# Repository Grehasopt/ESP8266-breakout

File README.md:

# ESP8266-breakout
A breadboard friendly ESP12E/F breakout with all I/O pins available, flash/reset buttons onboard, and pins ready to use with FTDI module

## License
This project is licensed under the CERN-OHL-S-2.0 (applies from the very first commit on Mar 7, 2021) with the added condition that it may not be used for commercial purposes without prior permission from the license holder.

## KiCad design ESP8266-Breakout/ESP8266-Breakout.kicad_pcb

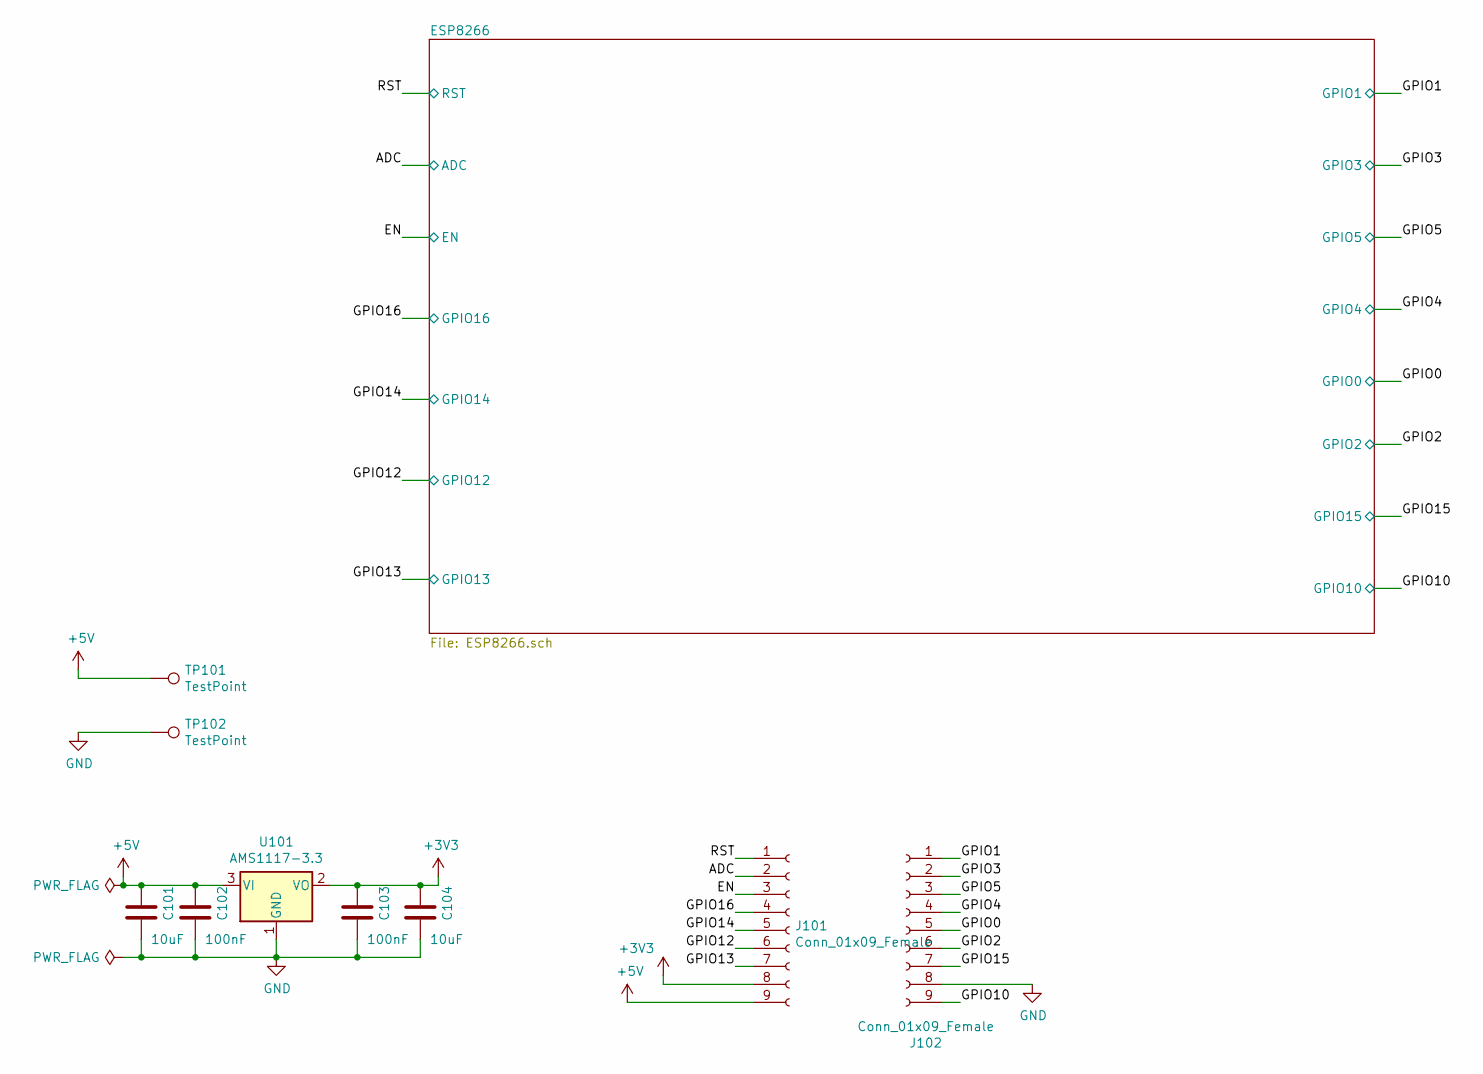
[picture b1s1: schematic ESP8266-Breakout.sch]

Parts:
C101, C104: 10uF; C_1206_3216Metric_Pad1.33x1.80mm_HandSolder; LCSC C13585
C102, C103: 100nF; C_1206_3216Metric_Pad1.33x1.80mm_HandSolder; LCSC C24497
J101, J102: Conn_01x09_Female; PinHeader_1x09_P2.54mm_Vertical_without_silkscrean
TP101, TP102: TestPoint; TestPoint_Pad_D3.0mm
U101: AMS1117-3.3; SOT-223-3_TabPin2

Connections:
+3V3: C103.1, C104.1, J101.8, U101.2 (VO); also elsewhere on the board
+5V: C101.1, C102.1, J101.9, TP101.1, U101.3 (VI)
/ADC: J101.2; also elsewhere on the board
/EN: J101.3; also elsewhere on the board
/GPIO0: J102.5; also elsewhere on the board
/GPIO1: J102.1; also elsewhere on the board
/GPIO2: J102.6; also elsewhere on the board
/GPIO3: J102.2; also elsewhere on the board
/GPIO4: J102.4; also elsewhere on the board
/GPIO5: J102.3; also elsewhere on the board
/GPIO10: J102.9; also elsewhere on the board
/GPIO12: J101.6; also elsewhere on the board
/GPIO13: J101.7; also elsewhere on the board
/GPIO14: J101.5; also elsewhere on the board
/GPIO15: J102.7; also elsewhere on the board
/GPIO16: J101.4; also elsewhere on the board
/RST: J101.1; also elsewhere on the board
GND: C101.2, C102.2, C103.2, C104.2, J102.8, TP102.1, U101.1 (GND); also elsewhere on the board

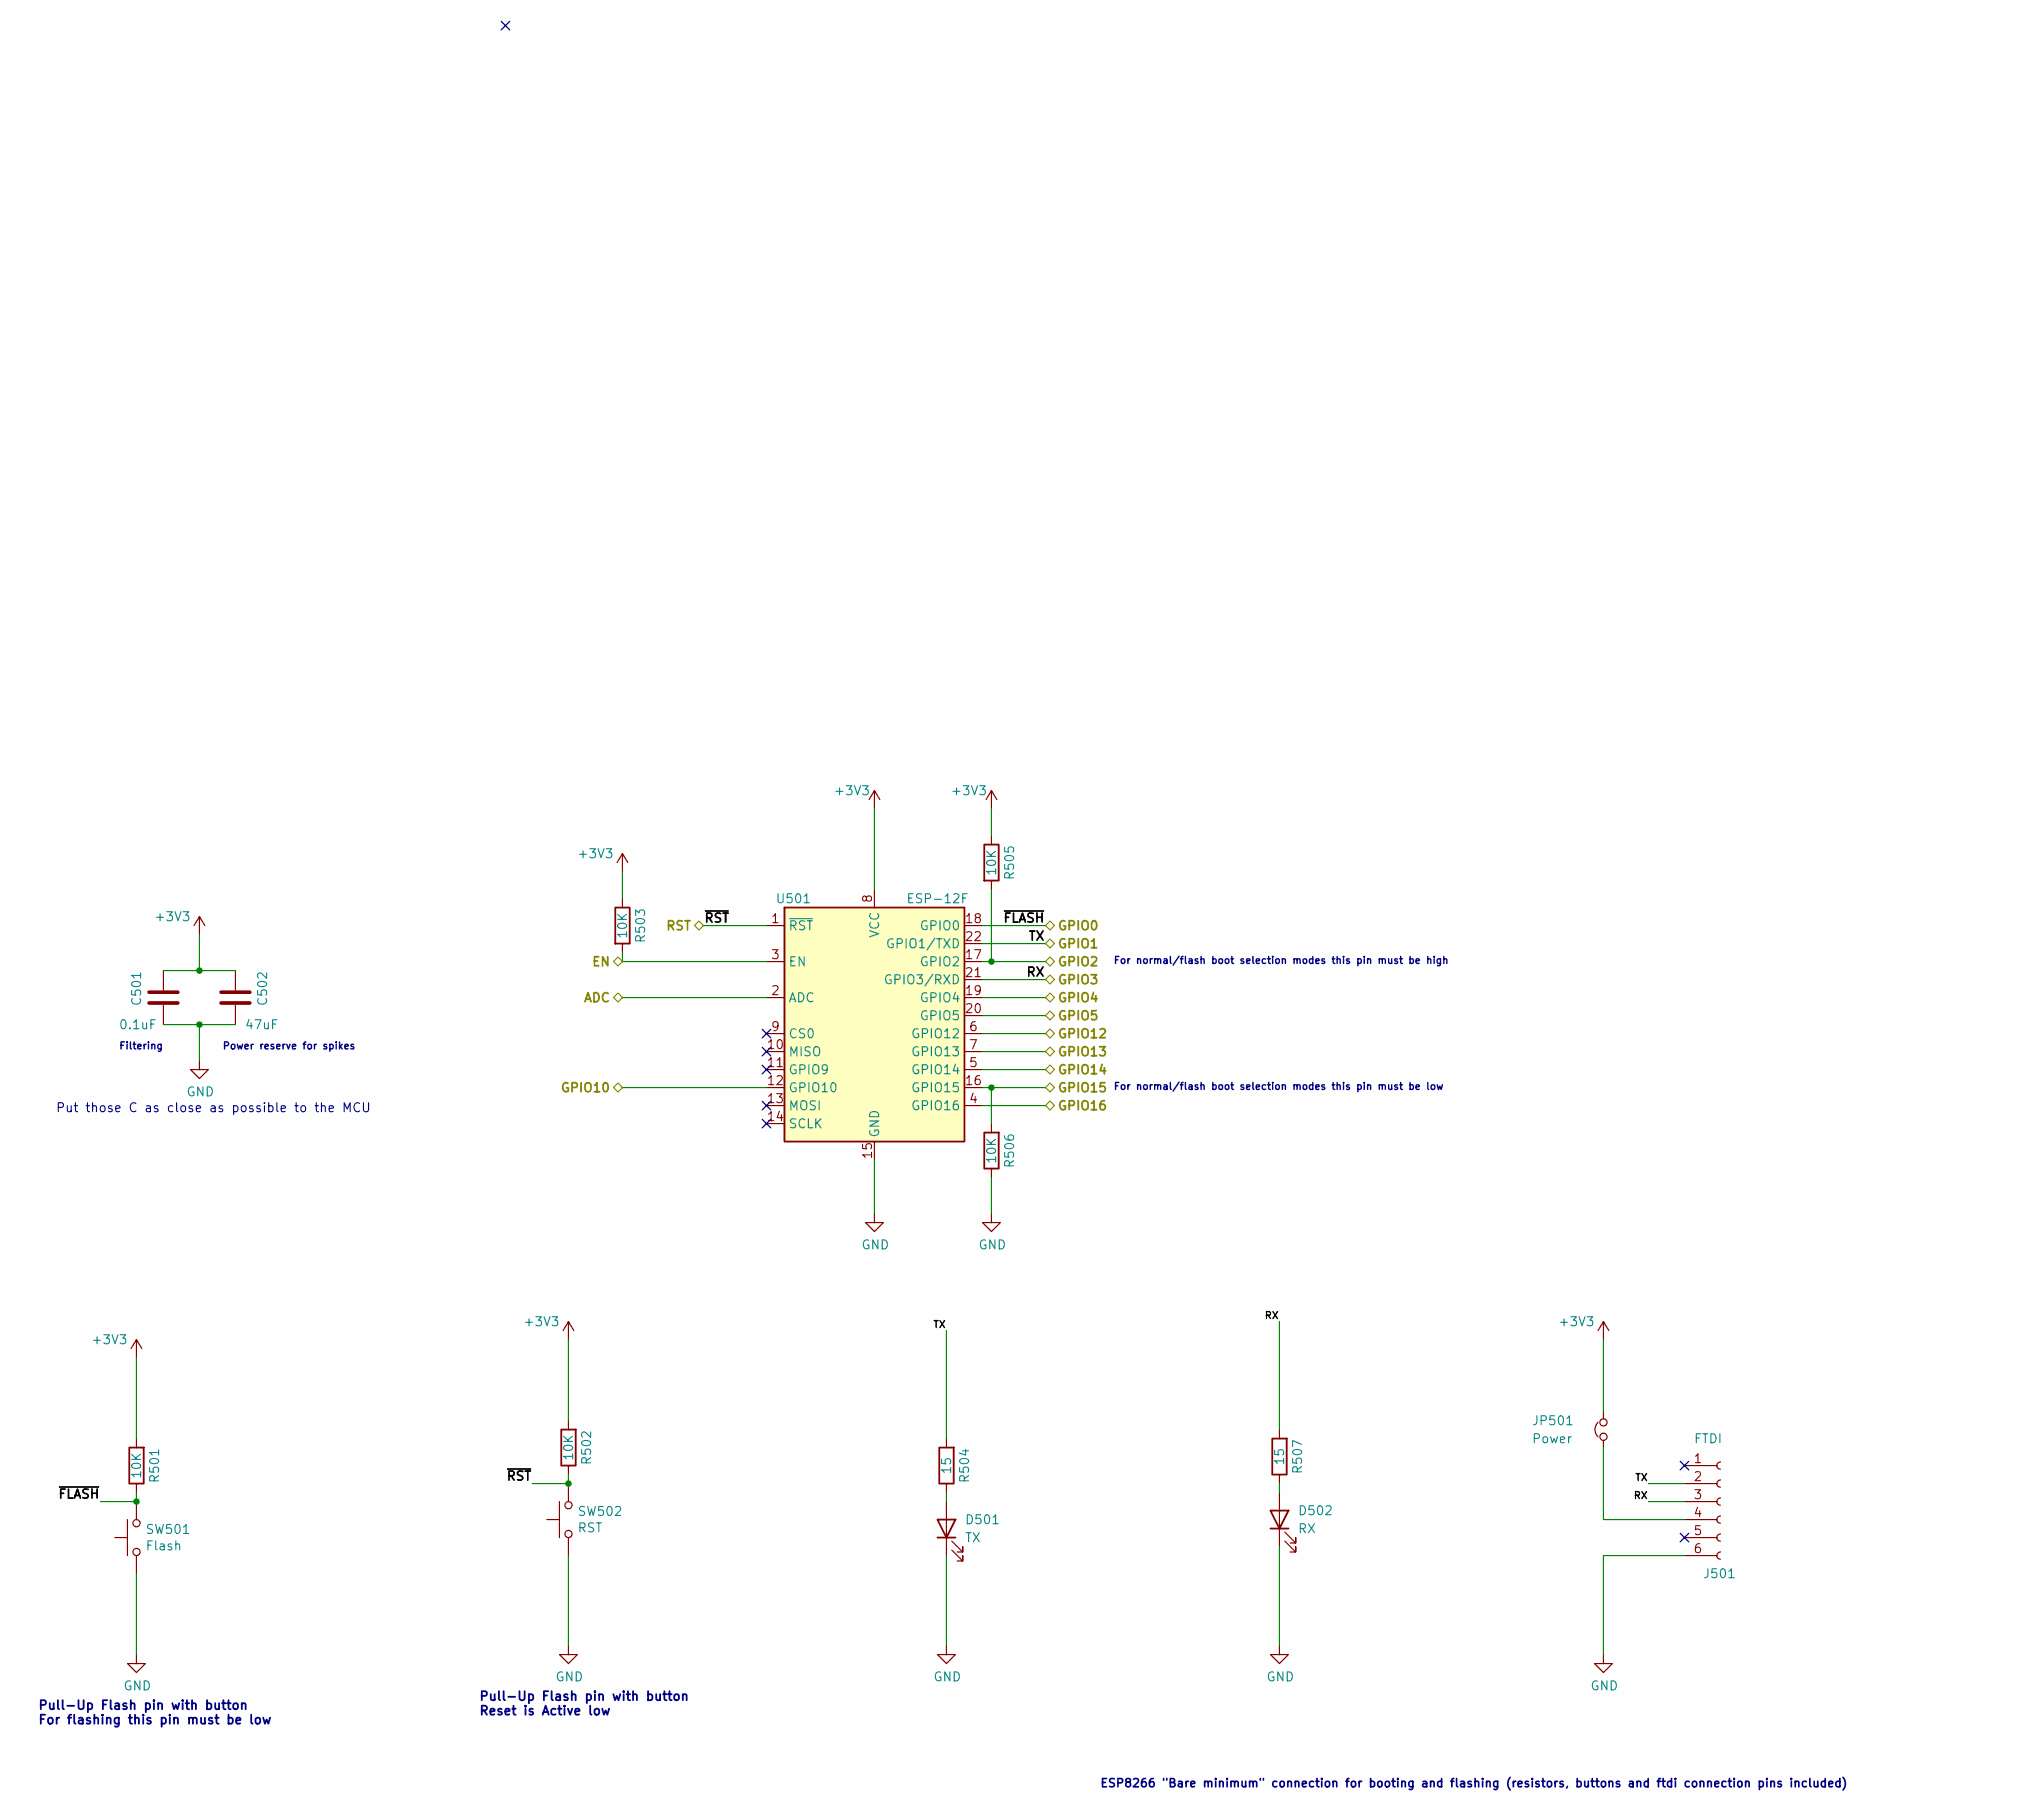
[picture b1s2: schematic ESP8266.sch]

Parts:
C501: 0.1uF; C_0603_1608Metric_Pad1.08x0.95mm_HandSolder; LCSC C14663
C502: 47uF; C_1206_3216Metric_Pad1.33x1.80mm_HandSolder; LCSC C96123
D501: TX; LED_0603_1608Metric_Pad1.05x0.95mm_HandSolder; LCSC C72041
D502: RX; LED_0603_1608Metric_Pad1.05x0.95mm_HandSolder; LCSC C72041
J501: FTDI; PinHeader_1x06_P2.54mm_Vertical
JP501: Power; SolderJumper-2_P1.3mm_Bridged_RoundedPad1.0x1.5mm
R501, R502, R503, R505, R506: 10K; R_0603_1608Metric_Pad0.98x0.95mm_HandSolder; LCSC C25804
R504, R507: 15; R_0805_2012Metric_Pad1.20x1.40mm_HandSolder; LCSC C17480
SW501: Flash; SW_SPST_CK_RS282G05A3; LCSC C398053
SW502: RST; SW_SPST_CK_RS282G05A3; LCSC C398053
U501: ESP-12F; ESP-12E; LCSC C82891

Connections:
+3V3: C501.1, C502.1, JP501.2, R501.2, R502.2, R503.1, R505.1, U501.8 (VCC); also elsewhere on the board
/ADC: U501.2 (ADC); also elsewhere on the board
/EN: R503.2, U501.3 (EN); also elsewhere on the board
/GPIO0: R501.1, SW501.2, U501.18 (GPIO0); also elsewhere on the board
/GPIO1: J501.2, R504.2, U501.22 (GPIO1/TXD); also elsewhere on the board
/GPIO2: R505.2, U501.17 (GPIO2); also elsewhere on the board
/GPIO3: J501.3, R507.2, U501.21 (GPIO3/RXD); also elsewhere on the board
/GPIO4: U501.19 (GPIO4); also elsewhere on the board
/GPIO5: U501.20 (GPIO5); also elsewhere on the board
/GPIO10: U501.12 (GPIO10); also elsewhere on the board
/GPIO12: U501.6 (GPIO12); also elsewhere on the board
/GPIO13: U501.7 (GPIO13); also elsewhere on the board
/GPIO14: U501.5 (GPIO14); also elsewhere on the board
/GPIO15: R506.2, U501.16 (GPIO15); also elsewhere on the board
/GPIO16: U501.4 (GPIO16); also elsewhere on the board
/RST: R502.1, SW502.2, U501.1 (~RST); also elsewhere on the board
GND: C501.2, C502.2, D501.1 (K), D502.1 (K), J501.6, R506.1, SW501.1, SW502.1, U501.15 (GND); also elsewhere on the board
unnamed: D501.2 (A), R504.1
unnamed: D502.2 (A), R507.1
unnamed: J501.4, JP501.1

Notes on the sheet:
ESP8266 "Bare minimum" connection for booting and flashing (resistors, buttons and ftdi connection pins included)
For normal/flash boot selection modes this pin must be high
For normal/flash boot selection modes this pin must be low
Pull-Up Flash pin with button Reset is Active low
Filtering
Power reserve for spikes
Pull-Up Flash pin with button For flashing this pin must be low
Put those C as close as possible to the MCU

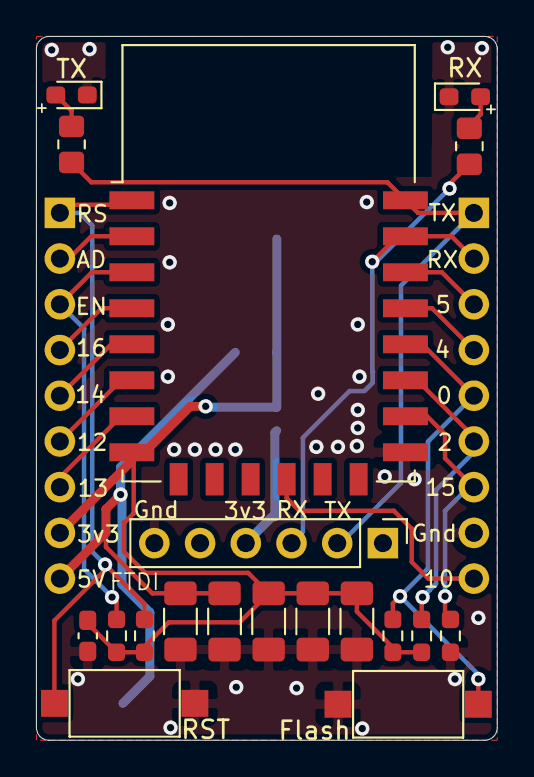
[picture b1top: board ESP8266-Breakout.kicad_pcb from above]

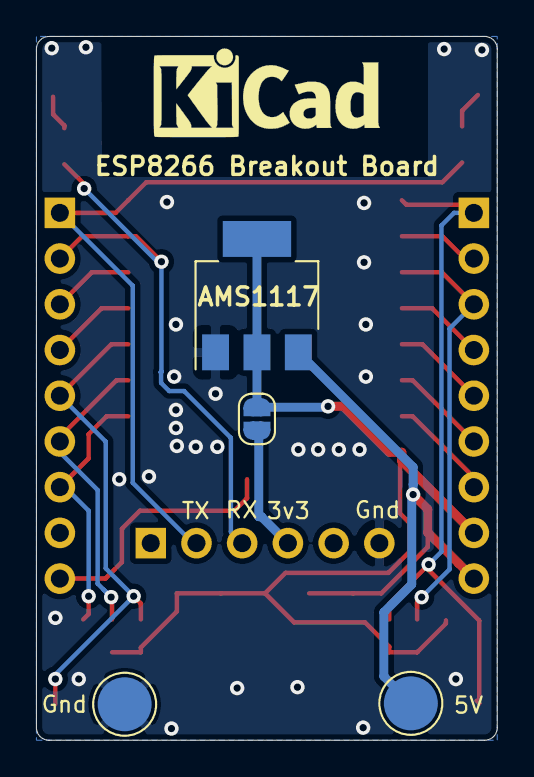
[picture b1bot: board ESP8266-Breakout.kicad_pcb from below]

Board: 2 copper layers, 25.6 x 39.1 mm, 25 parts (4 on the bottom side), 21 nets.

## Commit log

2021-07-18 Init - problem with scematic (empty)
2021-10-11 New version completed, shematic + pcb wired
2021-10-11 ESP8266 photo added
2021-11-28 Single and panel board views added
2022-01-07 Release 2
2025-01-31 Add photos
